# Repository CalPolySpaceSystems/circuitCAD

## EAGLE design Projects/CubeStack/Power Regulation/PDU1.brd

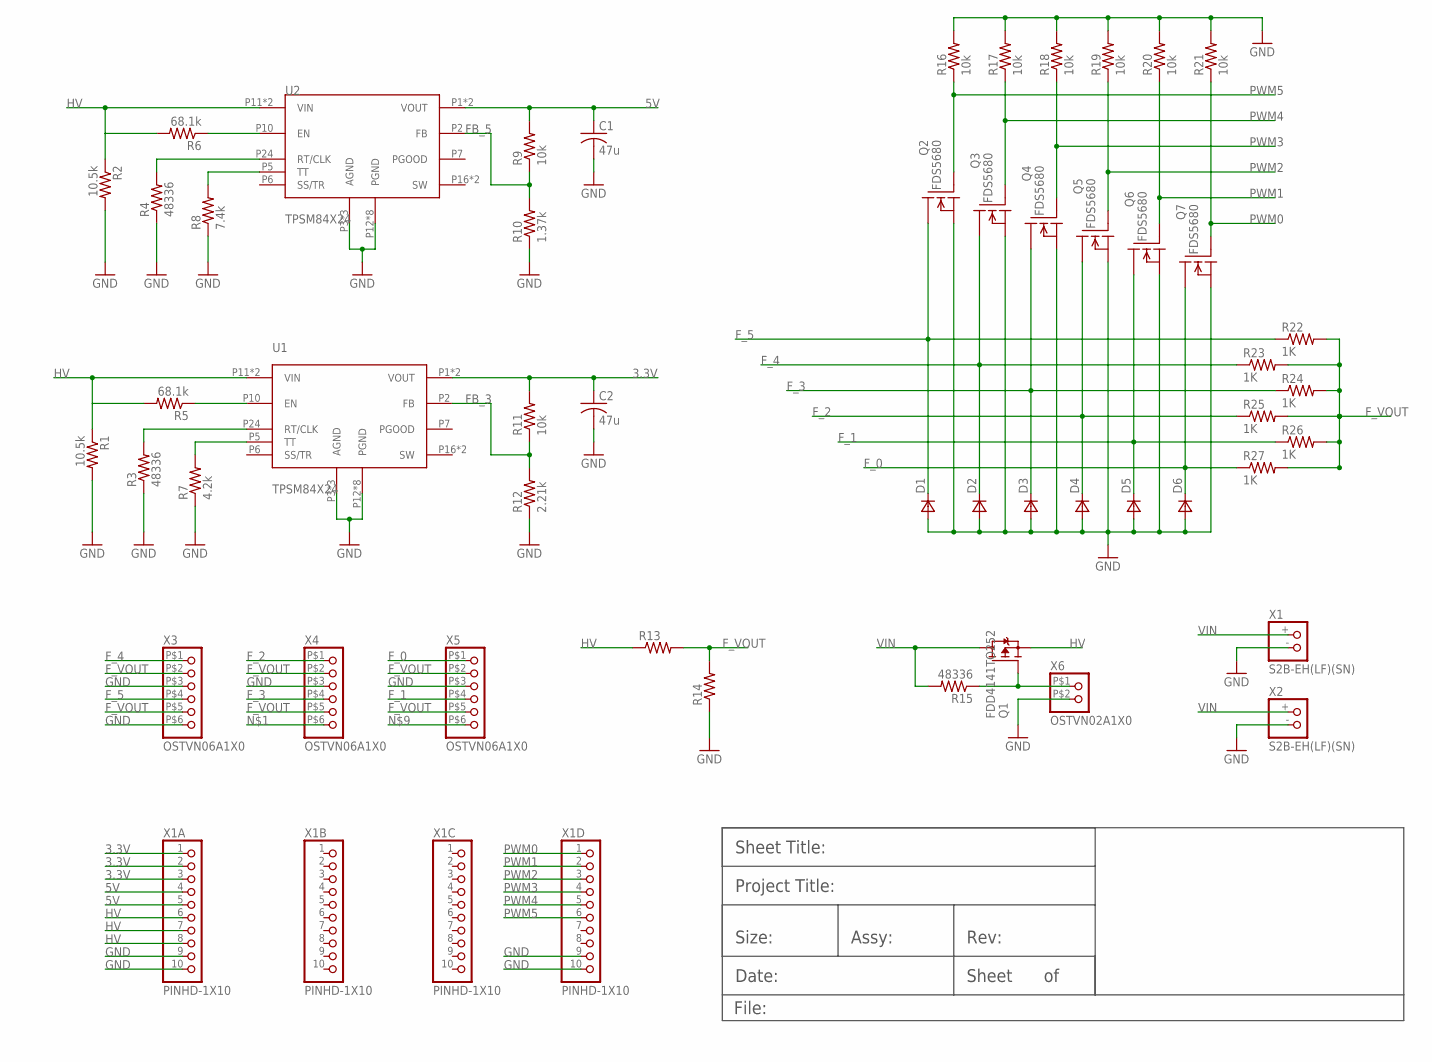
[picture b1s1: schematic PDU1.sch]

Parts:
C1, C2: 47u; C1206
D1, D2, D3, D4, D5, D6: DSOD323; SOD323
Q1: FDD4141TO252; TO252
Q2, Q3, Q4, Q5, Q6, Q7: FDS5680; SO-8
R1, R2: 10.5k; R1206
R3, R4, R15: 48336; R1206
R5, R6: 68.1k; R1206
R7: 4.2k; R1206
R8: 7.4k; R1206
R9, R11: 10k; R1206
R10: 1.37k; R1206
R12: 2.21k; R1206
R13, R14: R-US_R6332; R6332
R16, R17, R18, R19, R20, R21: 10k; R0603
R22, R23, R24, R25, R26, R27: 1K; R0603
U1, U2: TPSM84X24; QFM-5.4
X1, X2: S2B-EH(LF)(SN); S2B-EH
X1A, X1B, X1C, X1D: PINHD-1X10; 1X10-BIG
X3, X4, X5: OSTVN06A1X0
X6: OSTVN02A1X0

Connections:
3.3V: C2.1, R11.2, U1.P1 (VOUT), U1.P8 (VOUT), X1A.1, X1A.2, X1A.3
5V: C1.1, R9.2, U2.P1 (VOUT), U2.P8 (VOUT), X1A.4, X1A.5
EN: Q1.1 (G), R15.1, X6.P$1 (1)
FB_3: R11.1, R12.2, U1.P2 (FB)
FB_5: R9.1, R10.2, U2.P2 (FB)
F_0: D6.1 (C), Q7.5 (D), Q7.6 (D), Q7.7 (D), Q7.8 (D), R27.1, X5.P$1 (1)
F_1: D5.1 (C), Q6.5 (D), Q6.6 (D), Q6.7 (D), Q6.8 (D), R26.1, X5.P$4 (4)
F_2: D4.1 (C), Q5.5 (D), Q5.6 (D), Q5.7 (D), Q5.8 (D), R25.1, X4.P$1 (1)
F_3: D3.1 (C), Q4.5 (D), Q4.6 (D), Q4.7 (D), Q4.8 (D), R24.1, X4.P$4 (4)
F_4: D2.1 (C), Q3.5 (D), Q3.6 (D), Q3.7 (D), Q3.8 (D), R23.1, X3.P$1 (1)
F_5: D1.1 (C), Q2.5 (D), Q2.6 (D), Q2.7 (D), Q2.8 (D), R22.1, X3.P$4 (4)
F_VOUT: R13.2, R14.2, R22.2, R23.2, R24.2, R25.2, R26.2, R27.2, X3.P$2 (2), X3.P$5 (5), X4.P$2 (2), X4.P$5 (5), X5.P$2 (2), X5.P$5 (5)
GND: C1.2, C2.2, D1.2 (A), D2.2 (A), D3.2 (A), D4.2 (A), D5.2 (A), D6.2 (A), Q2.1 (S), Q2.2 (S), Q2.3 (S), Q3.1 (S), Q3.2 (S), Q3.3 (S), Q4.1 (S), Q4.2 (S), Q4.3 (S), Q5.1 (S), Q5.2 (S), Q5.3 (S), Q6.1 (S), Q6.2 (S), Q6.3 (S), Q7.1 (S), Q7.2 (S), Q7.3 (S), R1.2, R2.2, R3.1, R4.1, R7.1, R8.1, R10.1, R12.1, R14.1, R16.2, R17.2, R18.2, R19.2, R20.2, R21.2, U1.P3 (AGND), U1.P9 (AGND), U1.P12 (PGND), U1.P13 (PGND), U1.P14 (PGND), U1.P15 (PGND), U1.P18 (PGND), U1.P19 (PGND), U1.P20 (PGND), U1.P21 (PGND), U1.P23 (AGND), U2.P3 (AGND), U2.P9 (AGND), U2.P12 (PGND), U2.P13 (PGND), U2.P14 (PGND), U2.P15 (PGND), U2.P18 (PGND), U2.P19 (PGND), U2.P20 (PGND), U2.P21 (PGND), U2.P23 (AGND), X1.- (2), X1A.9, X1A.10, X1D.9, X1D.10, X2.- (2), X3.P$3 (3), X3.P$6 (6), X4.P$3 (3), X5.P$3 (3), X6.P$2 (2)
HV: Q1.2 (S), R1.1, R2.1, R5.2, R6.2, R13.1, U1.P11 (VIN), U1.P22 (VIN), U2.P11 (VIN), U2.P22 (VIN), X1A.6, X1A.7, X1A.8
unnamed: R4.2, U2.P24 (RT/CLK)
unnamed: R7.2, U1.P5 (TT)
unnamed: R3.2, U1.P24 (RT/CLK)
unnamed: R8.2, U2.P5 (TT)
unnamed: R6.1, U2.P10 (EN)
unnamed: R5.1, U1.P10 (EN)
PWM0: Q7.4 (G), R21.1, X1D.1
PWM1: Q6.4 (G), R20.1, X1D.2
PWM2: Q5.4 (G), R19.1, X1D.3
PWM3: Q4.4 (G), R18.1, X1D.4
PWM4: Q3.4 (G), R17.1, X1D.5
PWM5: Q2.4 (G), R16.1, X1D.6
VIN: Q1.3 (D), R15.2, X1.+ (1), X2.+ (1)

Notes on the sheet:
C:/Users/patri/Pictures/CPSSLOGO.bmp

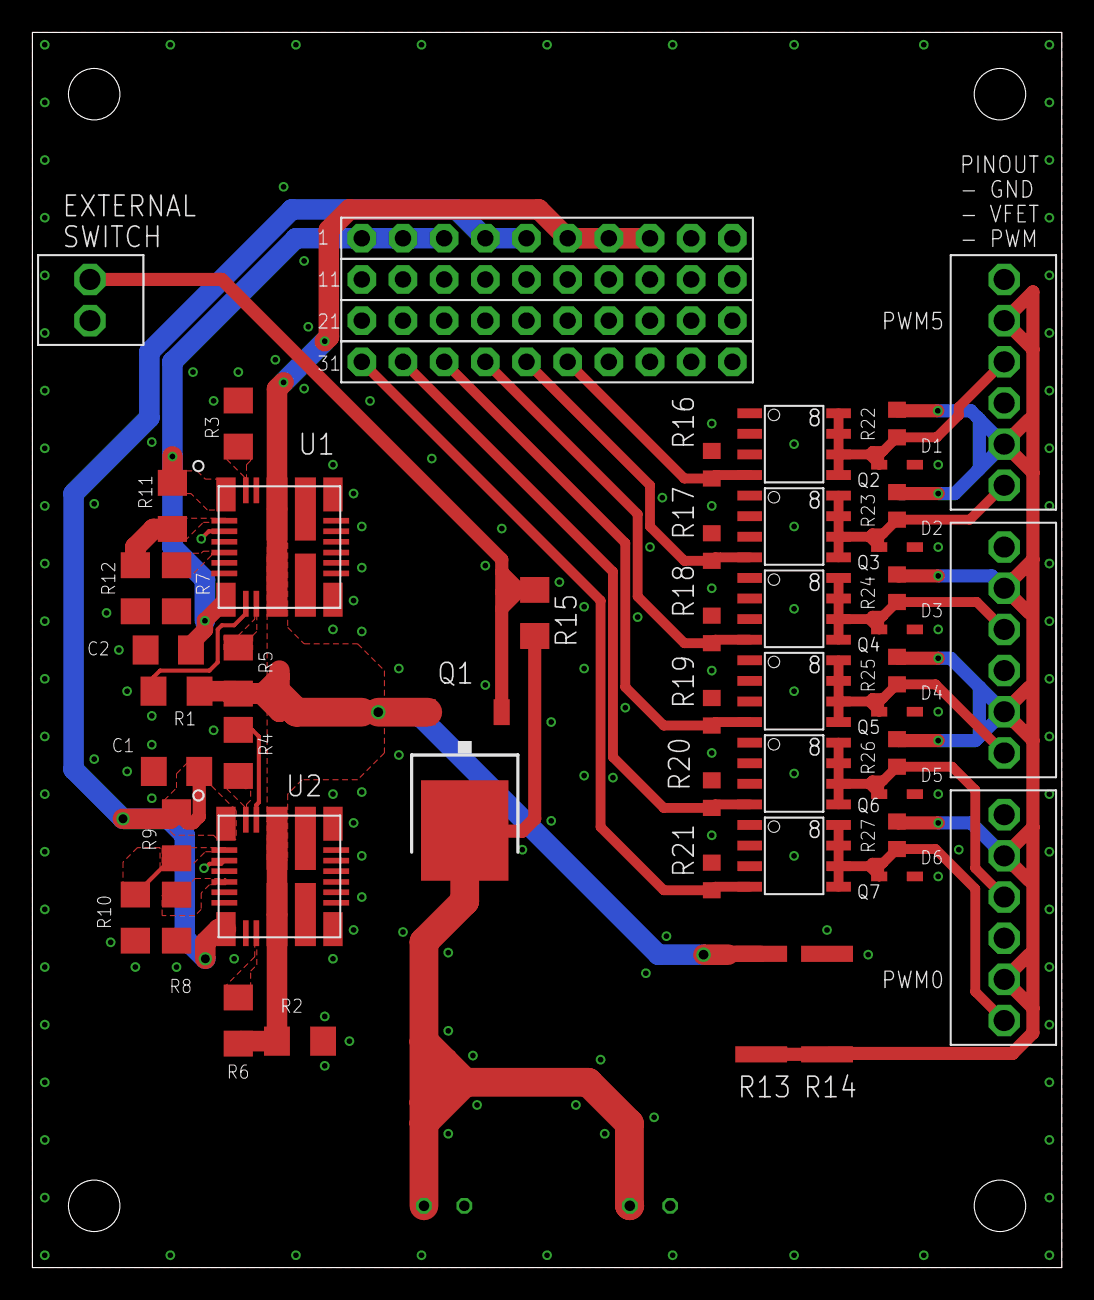
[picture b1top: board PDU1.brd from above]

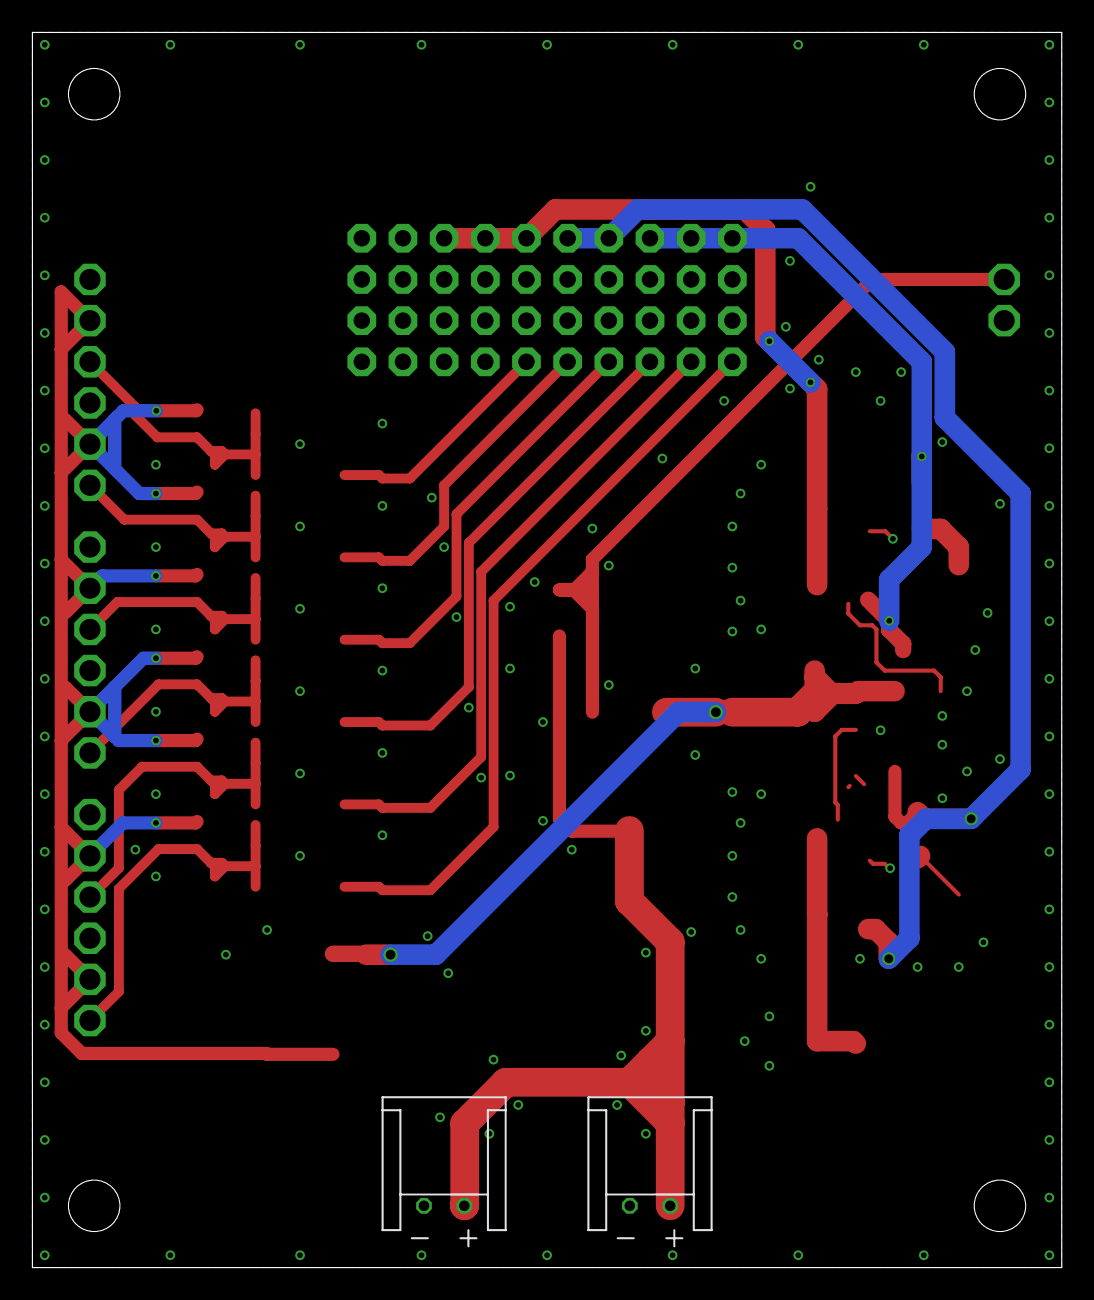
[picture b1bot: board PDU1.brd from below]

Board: 2 copper layers, 63.5 x 76.2 mm, 54 parts (2 on the bottom side), 27 nets.

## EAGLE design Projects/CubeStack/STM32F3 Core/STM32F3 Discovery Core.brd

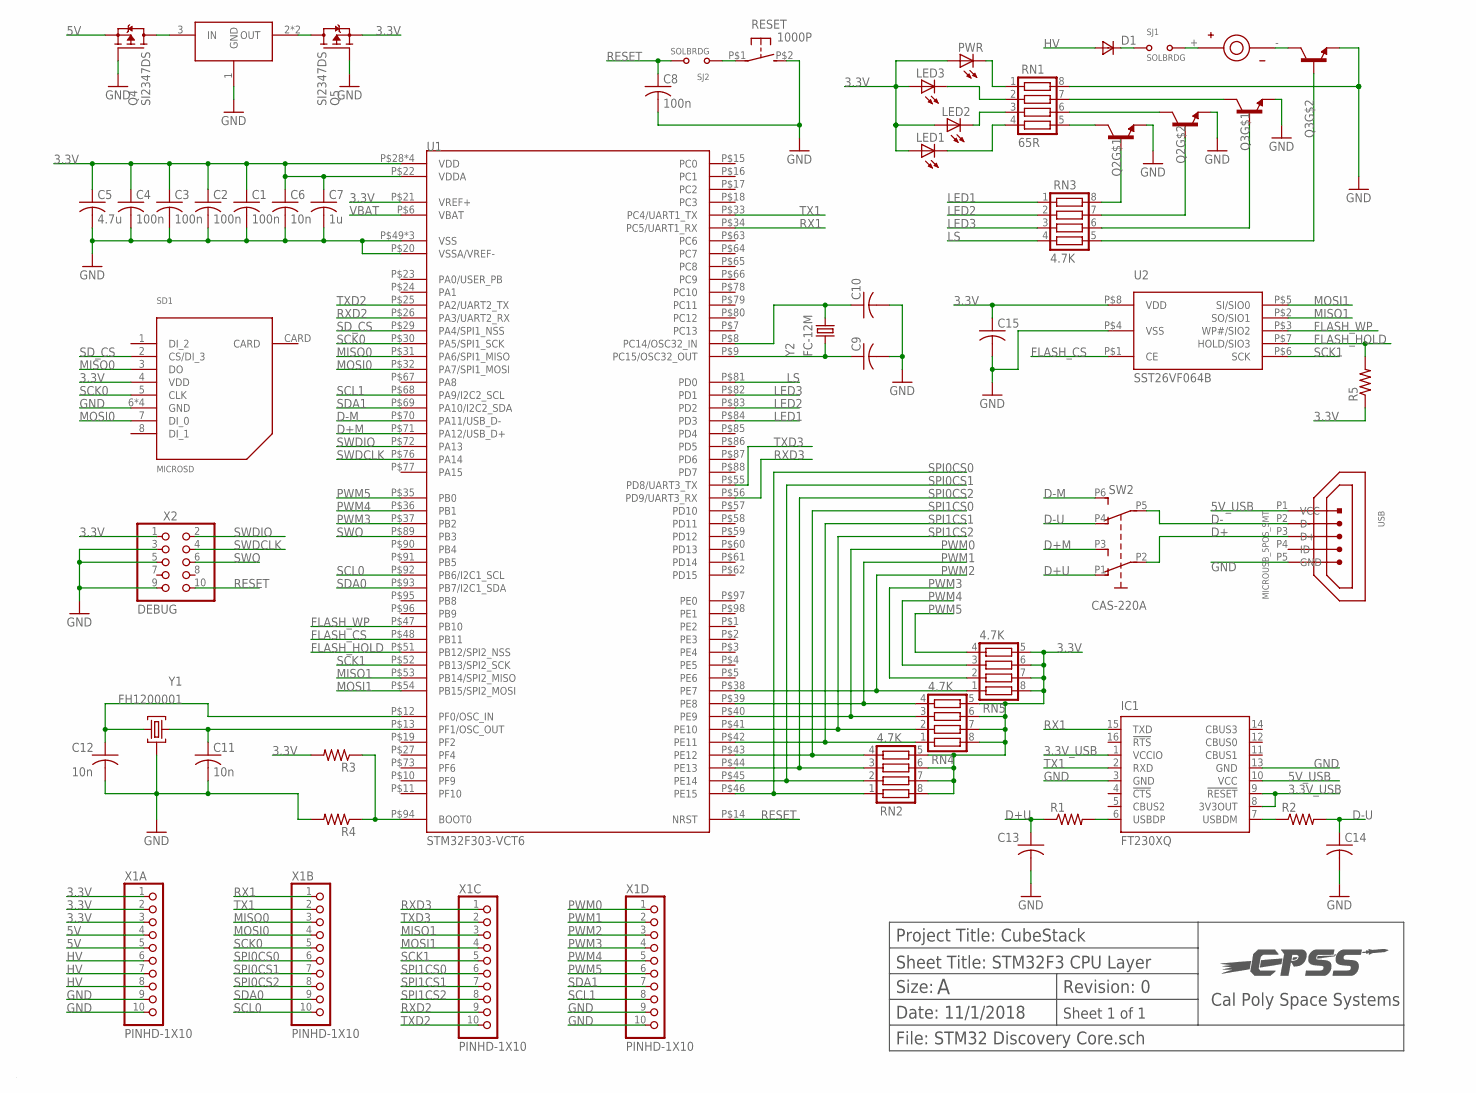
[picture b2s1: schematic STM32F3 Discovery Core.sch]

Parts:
C1, C2, C3, C4: 100n; C0805
C5: 4.7u; C0805
C6: 10n; C0805
C7: 1u; C0805
C8: 100n; C0603
C9, C10, C15: C-USC0402; C0402
C11, C12: 10n; C0402
C13, C14: C-USC0603; C0603
D1: DSOD323; SOD323
IC1: FT230XQ; QFN16
LED1, LED2, LED3: LEDCHIPLED_0805; CHIPLED_0805
LS1: AI-1440-TWT-24V-2-R; AI-1440-TWT-24-2-R
PWR: LEDCHIPLED_0805; CHIPLED_0805
Q2, Q3: MBT3904DW2T1; SOT-363
Q4, Q5: SI2347DS; SOT23
R1, R2, R3, R4, R5: R-US_R0603; R0603
RESET: 1000P; B3U-1000P
RN1: 65R; CTS742C083
RN2, RN3, RN4, RN5: 4.7K; CTS742C083
SD1: MICROSD; CONN_MICROSD
SJ1, SJ2: SOLBRDG
SW2: CAS-220A; CAS220B1
U1: STM32F303-VCT6; LQFP-100
U2: SST26VF064B; SOIJ
U3: AZ1117C; SOT89
USB: MICROUSB_5POS_SMT; RECPT_SMT_R/A
X1A, X1B, X1C, X1D: PINHD-1X10; 1X10-BIG
X2: DEBUG; 2X5-PTH-1.27MM
Y1: FH1200001; MINISMD
Y2: FC-12M

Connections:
3.3V: C1.1, C2.1, C3.1, C4.1, C5.1, C6.1, C7.1, C15.1, LED1.A, LED2.A, LED3.A, PWR.A, Q5.2 (S), R3.2, R5.1, RN2.5, RN2.6, RN2.7, RN2.8, RN4.5, RN4.6, RN4.7, RN4.8, RN5.5, RN5.6, RN5.7, RN5.8, SD1.4 (VDD), U1.P$21 (VREF+), U1.P$22 (VDDA), U1.P$28 (VDD), U1.P$50 (VDD), U1.P$75 (VDD), U1.P$100 (VDD), U2.P$8 (VDD), X1A.1, X1A.2, X1A.3, X2.1
3.3V_USB: IC1.1 (VCCIO), IC1.8 (3V3OUT), IC1.9 (!RESET), Q5.3 (D), U3.2 (OUT), U3.2@1 (OUT)
5V: Q4.2 (S), X1A.4, X1A.5
5V_USB: IC1.10 (VCC), Q4.3 (D), U3.3 (IN), USB.P1 (VCC)
D+: SW2.P2, USB.P3 (D+)
D+M: SW2.P3 (S), U1.P$71 (PA12/USB_D+)
D+U: C13.1, R1.1, SW2.P1 (O)
D-: SW2.P5 (P1), USB.P2 (D-)
D-M: SW2.P6 (S1), U1.P$70 (PA11/USB_D-)
D-U: C14.1, R2.2, SW2.P4 (O1)
FLASH_CS: U1.P$48 (PB11), U2.P$1 (CE)
FLASH_HOLD: R5.2, U1.P$51 (PB12/SPI2_NSS), U2.P$7 (HOLD/SIO3)
FLASH_WP: U1.P$47 (PB10), U2.P$3 (WP#/SIO2)
GND: C1.2, C2.2, C3.2, C4.2, C5.2, C6.2, C7.2, C8.2, C9.2, C10.2, C11.2, C12.2, C13.2, C14.2, C15.2, IC1.3 (GND), IC1.13 (GND), Q2.P$3 (E), Q2.P$6 (E), Q3.P$3 (E), Q3.P$6 (E), Q4.1 (G), Q5.1 (G), R4.2, RESET.P$2 (S), RN1.8, SD1.6 (GND), SD1.GND1 (GND), SD1.GND2 (GND), SD1.GND3 (GND), U1.P$20 (VSSA/VREF-), U1.P$49 (VSS), U1.P$74 (VSS), U1.P$99 (VSS), U2.P$4 (VSS), U3.1 (GND), USB.P5 (GND), X1A.9, X1A.10, X1D.9, X1D.10, X2.3, X2.5, X2.9, Y1.GND2 (2), Y1.GND4 (2)
HV: D1.2 (A), X1A.6, X1A.7, X1A.8
LED1: RN3.1, U1.P$84 (PD3)
LED2: RN3.2, U1.P$83 (PD2)
LED3: RN3.3, U1.P$82 (PD1)
LS: RN3.4, U1.P$81 (PD0)
LS_D: LS1.-, Q3.P$5 (C)
LS_G: Q3.P$1 (B), RN3.5
L_1: LED1.C, RN1.4
L_1_D: Q2.P$4 (C), RN1.5
L_1_G: Q2.P$2 (B), RN3.8
L_2: LED2.C, RN1.3
L_2_D: Q2.P$5 (C), RN1.6
L_2_G: Q2.P$1 (B), RN3.7
L_3: LED3.C, RN1.2
L_3_D: Q3.P$4 (C), RN1.7
L_3_G: Q3.P$2 (B), RN3.6
L_PWR_D: PWR.C, RN1.1
MISO0: SD1.3 (DO), U1.P$31 (PA6/SPI1_MISO), X1B.3
MISO1: U1.P$53 (PB14/SPI2_MISO), U2.P$2 (SO/SIO1), X1C.3
MOSI0: SD1.7 (DI_0), U1.P$32 (PA7/SPI1_MOSI), X1B.4
MOSI1: U1.P$54 (PB15/SPI2_MOSI), U2.P$5 (SI/SIO0), X1C.4
unnamed: LS1.+, SJ1.P$2
unnamed: C10.1, U1.P$8 (PC14/OSC32_IN), Y2.2
unnamed: RESET.P$1, SJ2.P$1
unnamed: C9.1, U1.P$9 (PC15/OSC32_OUT), Y2.1
unnamed: C12.1, U1.P$12 (PF0/OSC_IN), Y1.P3 (3)
unnamed: C11.1, U1.P$13 (PF1/OSC_OUT), Y1.P1 (1)
unnamed: D1.1 (C), SJ1.P$1
unnamed: IC1.6 (USBDP), R1.2
unnamed: IC1.7 (USBDM), R2.1
unnamed: R3.1, R4.1, U1.P$94 (BOOT0)
PWM0: RN4.3, U1.P$40 (PE9), X1D.1
PWM1: RN4.4, U1.P$39 (PE8), X1D.2
PWM2: RN5.1, U1.P$38 (PE7), X1D.3
PWM3: RN5.2, U1.P$37 (PB2), X1D.4
PWM4: RN5.3, U1.P$36 (PB1), X1D.5
PWM5: RN5.4, U1.P$35 (PB0), X1D.6
RESET: C8.1, SJ2.P$2, U1.P$14 (NRST), X2.10
RX1: IC1.15 (TXD), U1.P$34 (PC5/UART1_RX), X1B.1
RXD2: U1.P$26 (PA3/UART2_RX), X1C.9
RXD3: U1.P$56 (PD9/UART3_RX), X1C.1
SCK0: SD1.5 (CLK), U1.P$30 (PA5/SPI1_SCK), X1B.5
SCK1: U1.P$52 (PB13/SPI2_SCK), U2.P$6 (SCK), X1C.5
SCL0: U1.P$92 (PB6/I2C1_SCL), X1B.10
SCL1: U1.P$68 (PA9/I2C2_SCL), X1D.8
SDA0: U1.P$93 (PB7/I2C1_SDA), X1B.9
SDA1: U1.P$69 (PA10/I2C2_SDA), X1D.7
SD_CS: SD1.2 (CS/DI_3), U1.P$29 (PA4/SPI1_NSS)
SPI0CS0: RN2.1, U1.P$46 (PE15), X1B.6
SPI0CS1: RN2.2, U1.P$45 (PE14), X1B.7
SPI0CS2: RN2.3, U1.P$44 (PE13), X1B.8
SPI1CS0: RN2.4, U1.P$43 (PE12), X1C.6
SPI1CS1: RN4.1, U1.P$42 (PE11), X1C.7
SPI1CS2: RN4.2, U1.P$41 (PE10), X1C.8
SWDCLK: U1.P$76 (PA14), X2.4
SWDIO: U1.P$72 (PA13), X2.2
SWO: U1.P$89 (PB3), X2.6
TX1: IC1.2 (RXD), U1.P$33 (PC4/UART1_TX), X1B.2
TXD2: U1.P$25 (PA2/UART2_TX), X1C.10
TXD3: U1.P$55 (PD8/UART3_TX), X1C.2
VBAT: U1.P$6 (VBAT)

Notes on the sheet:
Size:
Revision: 0
Sheet 1 of 1
Date: 11/1/2018
Sheet Title: STM32F3 CPU Layer
Project Title: CubeStack
File: STM32 Discovery Core.sch
Cal Poly Space Systems
C:/Users/patri/Pictures/CPSSLOGO.bmp

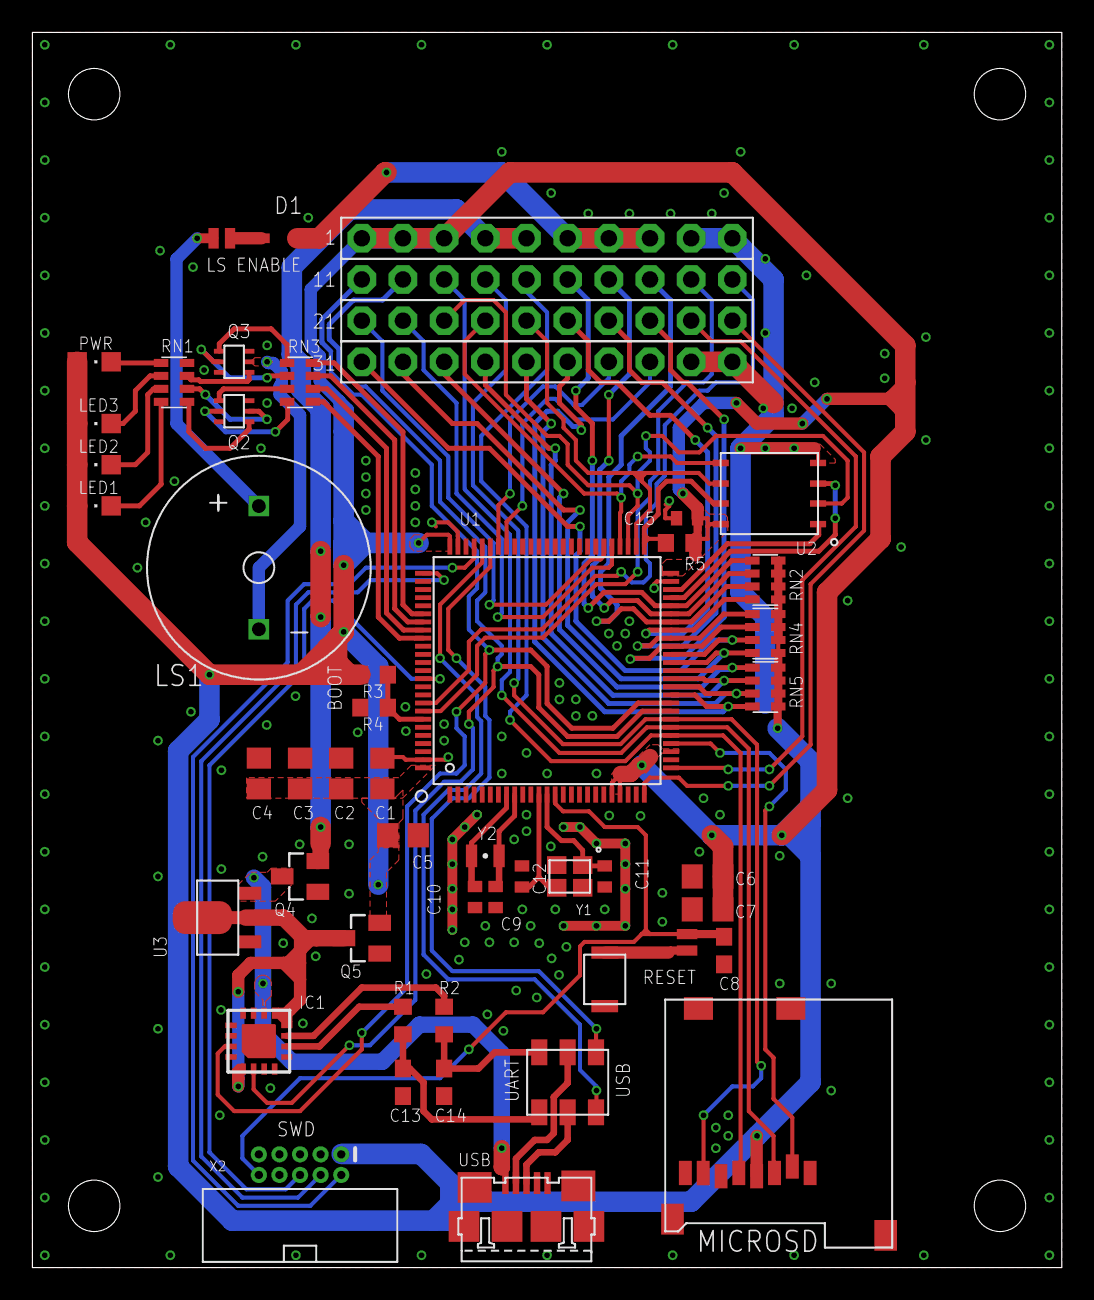
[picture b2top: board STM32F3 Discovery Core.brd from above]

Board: 2 copper layers, 63.5 x 76.2 mm, 52 parts (0 on the bottom side), 74 nets.

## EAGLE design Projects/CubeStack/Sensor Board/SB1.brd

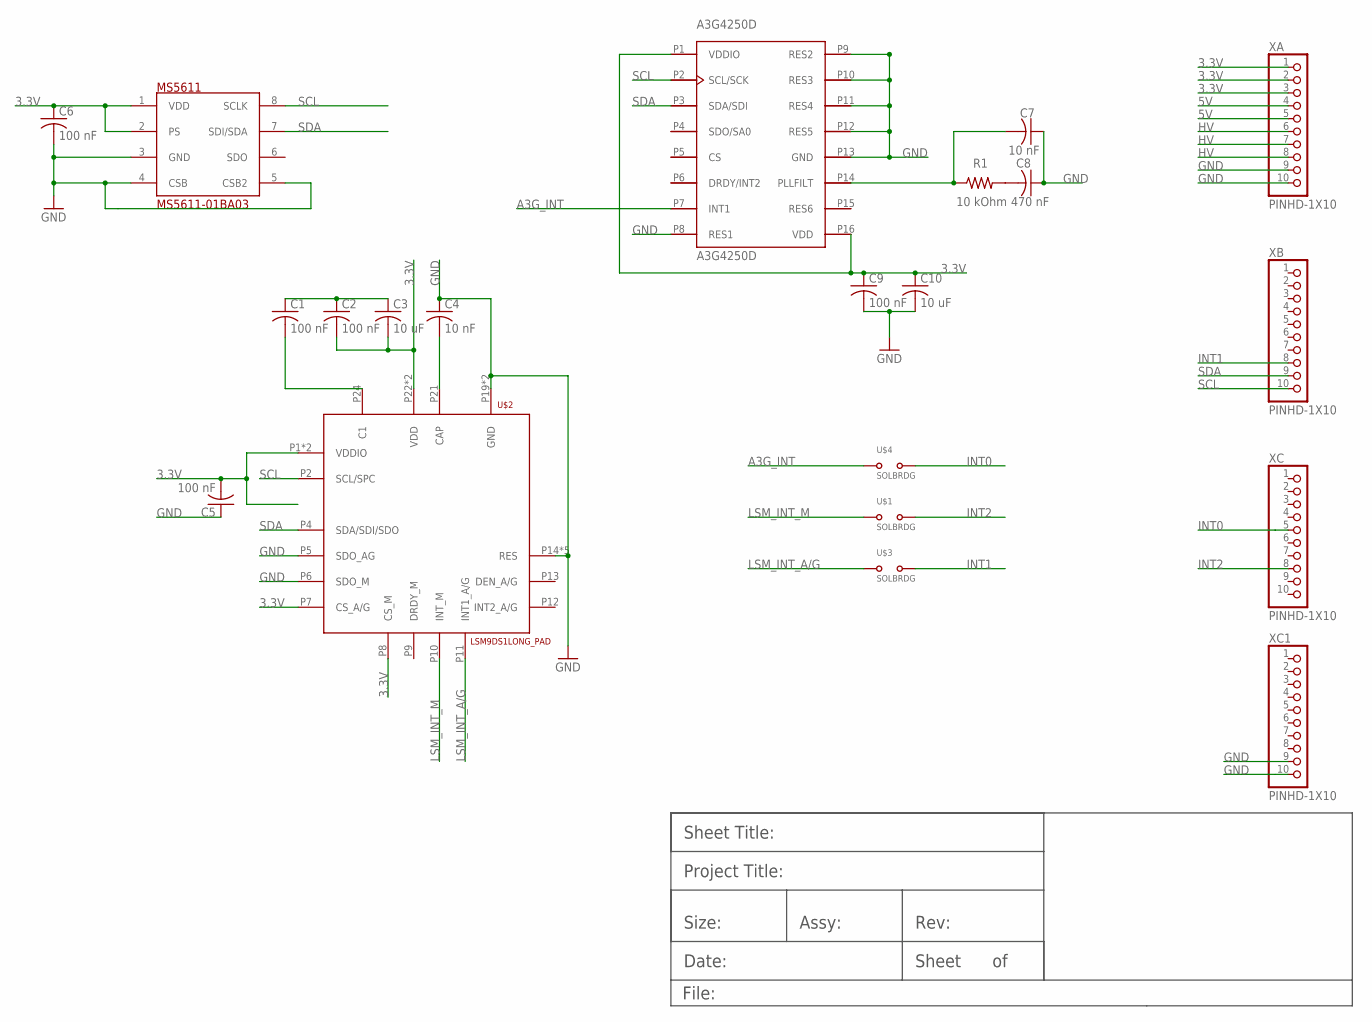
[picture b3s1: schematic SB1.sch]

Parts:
A3G4250D: A3G4250D; LGA-16
C1, C2, C5, C6, C9: 100 nF; C0603
C3, C10: 10 uF; C0603
C4, C7: 10 nF; C0603
C8: 470 nF; C0603
MS5611: MS5611-01BA03
R1: 10 kOhm; R0603
U$1, U$3, U$4: SOLBRDG
U$2: LSM9DS1LONG_PAD; LGA
XA: PINHD-1X10; 1X10-BIG
XB: PINHD-1X10; 1X10-BIG
XC, XC1: PINHD-1X10; 1X10-BIG

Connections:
3.3V: A3G4250D.P1 (VDDIO), A3G4250D.P16 (VDD), C2.2, C3.2, C5.2, C6.1, C9.1, C10.1, MS5611.1 (VDD), MS5611.2 (PS), U$2.P1 (VDDIO), U$2.P3 (VDDIO), U$2.P7 (CS_A/G), U$2.P8 (CS_M), U$2.P22 (VDD), U$2.P23 (VDD), XA.1, XA.2, XA.3
5V: XA.4, XA.5
A3G_INT: A3G4250D.P7 (INT1), U$4.P$1
GND: A3G4250D.P8 (RES1), A3G4250D.P9 (RES2), A3G4250D.P10 (RES3), A3G4250D.P11 (RES4), A3G4250D.P12 (RES5), A3G4250D.P13 (GND), C1.1, C2.1, C3.1, C4.1, C5.1, C6.2, C7.1, C8.1, C9.2, C10.2, MS5611.3 (GND), MS5611.4 (CSB), MS5611.5 (CSB2), U$2.P5 (SDO_AG), U$2.P6 (SDO_M), U$2.P14 (RES), U$2.P15 (RES), U$2.P16 (RES), U$2.P17 (RES), U$2.P18 (RES), U$2.P19 (GND), U$2.P20 (GND), XA.9, XA.10, XC1.9, XC1.10
HV: XA.6, XA.7, XA.8
INT0: U$4.P$2, XC.5
INT1: U$3.P$2, XB.8
INT2: U$1.P$2, XC.8
LSM_INT_A/G: U$2.P11 (INT1_A/G), U$3.P$1
LSM_INT_M: U$1.P$1, U$2.P10 (INT_M)
unnamed: A3G4250D.P14 (PLLFILT), C7.2, R1.1
unnamed: C8.2, R1.2
unnamed: C4.2, U$2.P21 (CAP)
unnamed: C1.2, U$2.P24 (C1)
SCL: A3G4250D.P2 (SCL/SCK), MS5611.8 (SCLK), U$2.P2 (SCL/SPC), XB.10
SDA: A3G4250D.P3 (SDA/SDI), MS5611.7 (SDI/SDA), U$2.P4 (SDA/SDI/SDO), XB.9

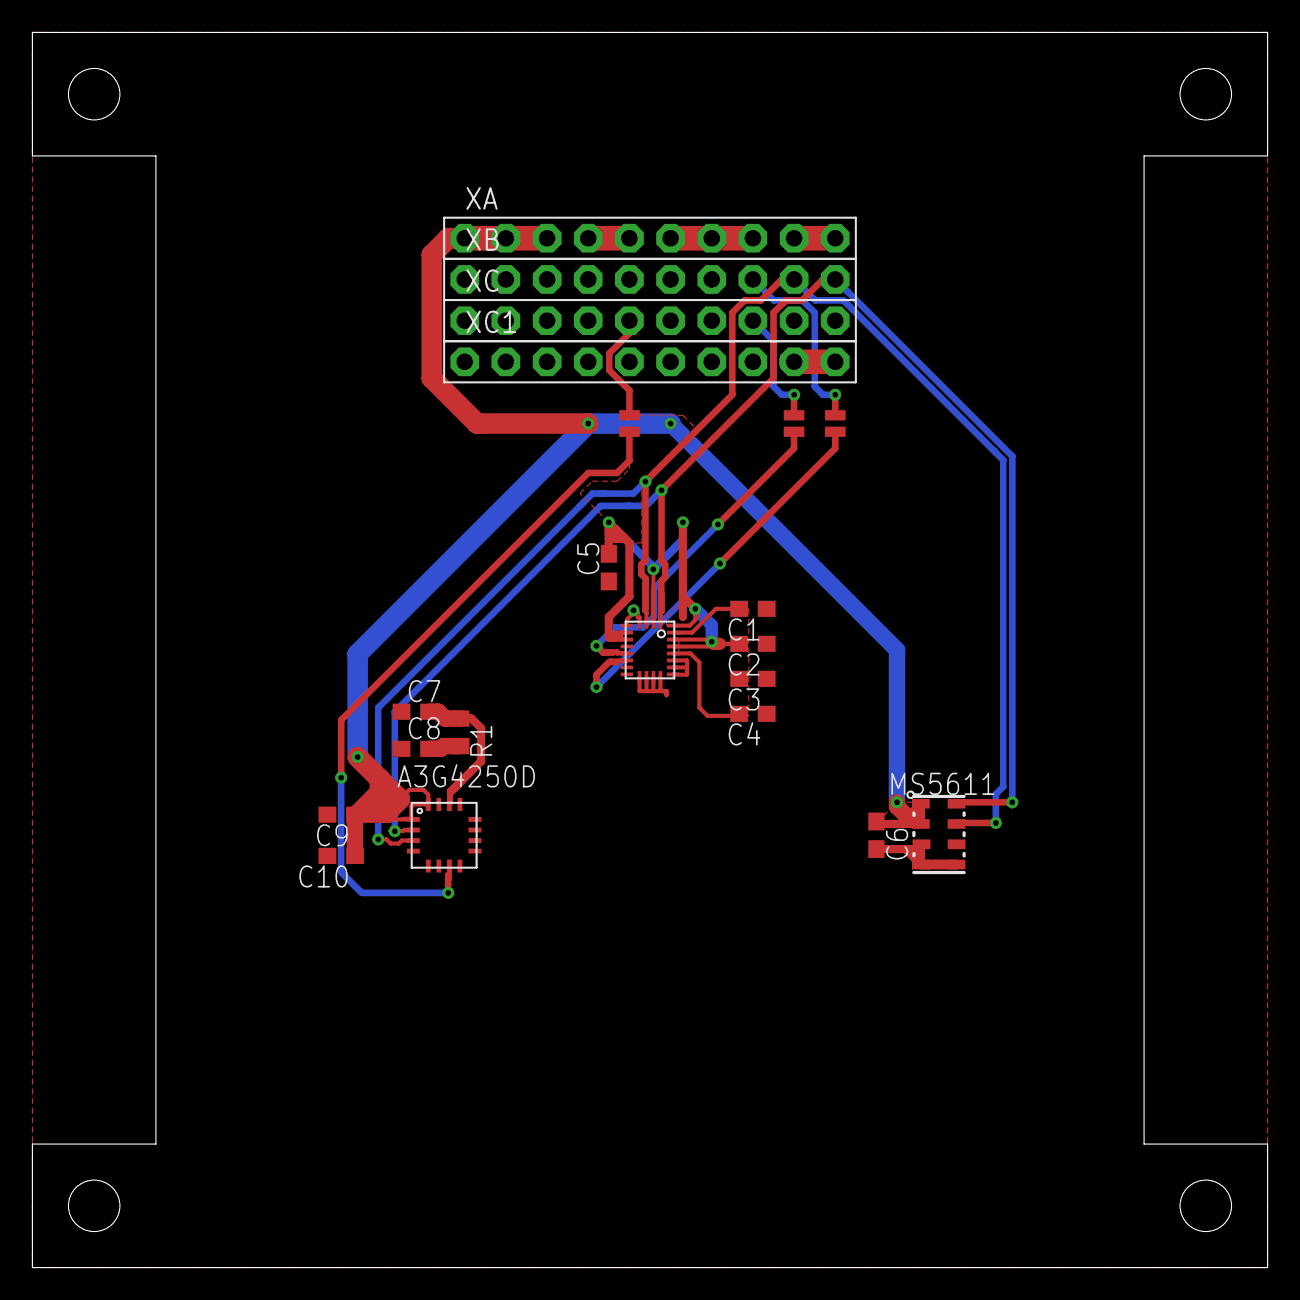
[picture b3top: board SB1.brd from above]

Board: 2 copper layers, 76.2 x 76.2 mm, 21 parts (0 on the bottom side), 16 nets.

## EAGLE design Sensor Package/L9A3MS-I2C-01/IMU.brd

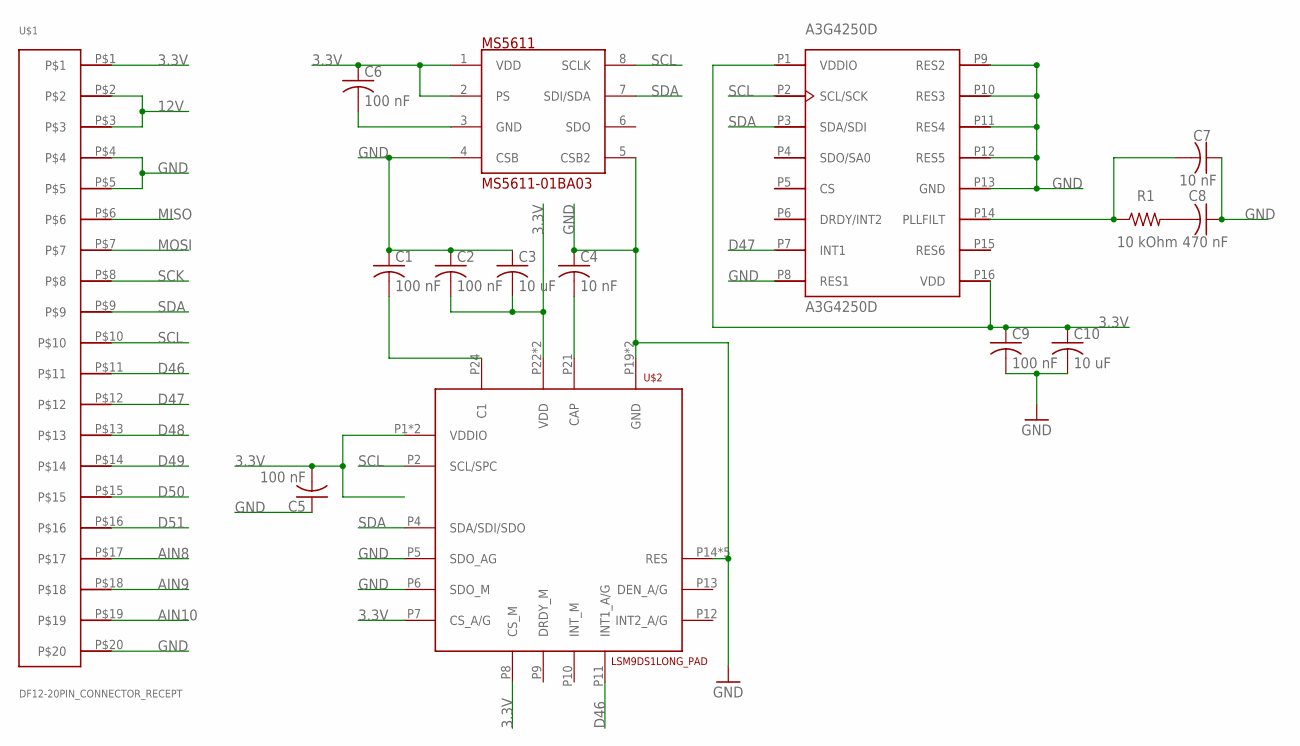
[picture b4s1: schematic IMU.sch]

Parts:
A3G4250D: A3G4250D; LGA-16
C1, C2, C5, C6, C9: 100 nF; C0603
C3, C10: 10 uF; C0603
C4, C7: 10 nF; C0603
C8: 470 nF; C0603
MS5611: MS5611-01BA03
R1: 10 kOhm; R0603
U$1: DF12-20PIN_CONNECTOR_RECEPT; DF12-RECEPT
U$2: LSM9DS1LONG_PAD; LGA

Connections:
3.3V: A3G4250D.P1 (VDDIO), A3G4250D.P16 (VDD), C2.2, C3.2, C5.2, C6.1, C9.1, C10.1, MS5611.1 (VDD), MS5611.2 (PS), U$1.P$1, U$2.P1 (VDDIO), U$2.P3 (VDDIO), U$2.P7 (CS_A/G), U$2.P8 (CS_M), U$2.P22 (VDD), U$2.P23 (VDD)
12V: U$1.P$2, U$1.P$3
AIN8: U$1.P$17
AIN9: U$1.P$18
AIN10: U$1.P$19
D46: U$1.P$11, U$2.P11 (INT1_A/G)
D47: A3G4250D.P7 (INT1), U$1.P$12
D48: U$1.P$13
D49: U$1.P$14
D50: U$1.P$15
D51: U$1.P$16
GND: A3G4250D.P8 (RES1), A3G4250D.P9 (RES2), A3G4250D.P10 (RES3), A3G4250D.P11 (RES4), A3G4250D.P12 (RES5), A3G4250D.P13 (GND), C1.1, C2.1, C3.1, C4.1, C5.1, C7.1, C8.1, C9.2, C10.2, MS5611.4 (CSB), MS5611.5 (CSB2), U$1.P$4, U$1.P$5, U$1.P$20, U$2.P5 (SDO_AG), U$2.P6 (SDO_M), U$2.P14 (RES), U$2.P15 (RES), U$2.P16 (RES), U$2.P17 (RES), U$2.P18 (RES), U$2.P19 (GND), U$2.P20 (GND)
MISO: U$1.P$6
MOSI: U$1.P$7
unnamed: A3G4250D.P14 (PLLFILT), C7.2, R1.1
unnamed: C8.2, R1.2
unnamed: C6.2, MS5611.3 (GND)
unnamed: C4.2, U$2.P21 (CAP)
unnamed: C1.2, U$2.P24 (C1)
SCK: U$1.P$8
SCL: A3G4250D.P2 (SCL/SCK), MS5611.8 (SCLK), U$1.P$10, U$2.P2 (SCL/SPC)
SDA: A3G4250D.P3 (SDA/SDI), MS5611.7 (SDI/SDA), U$1.P$9, U$2.P4 (SDA/SDI/SDO)

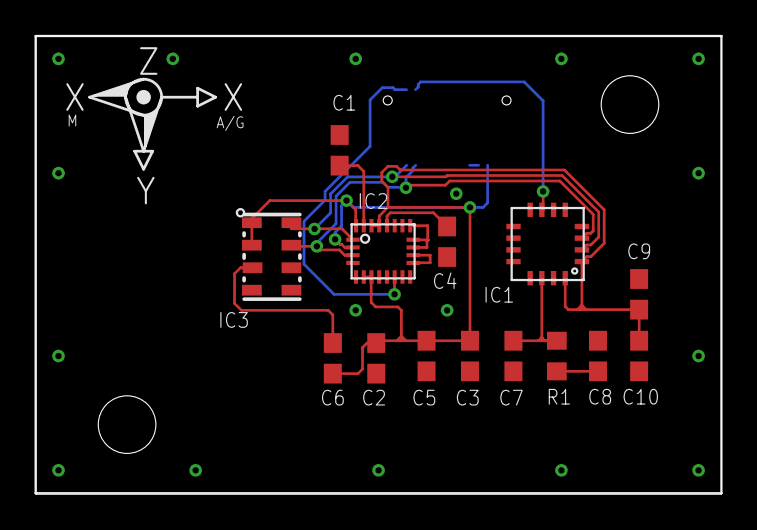
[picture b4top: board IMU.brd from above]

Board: 2 copper layers, 38.1 x 25.5 mm, 15 parts (0 on the bottom side), 12 nets.

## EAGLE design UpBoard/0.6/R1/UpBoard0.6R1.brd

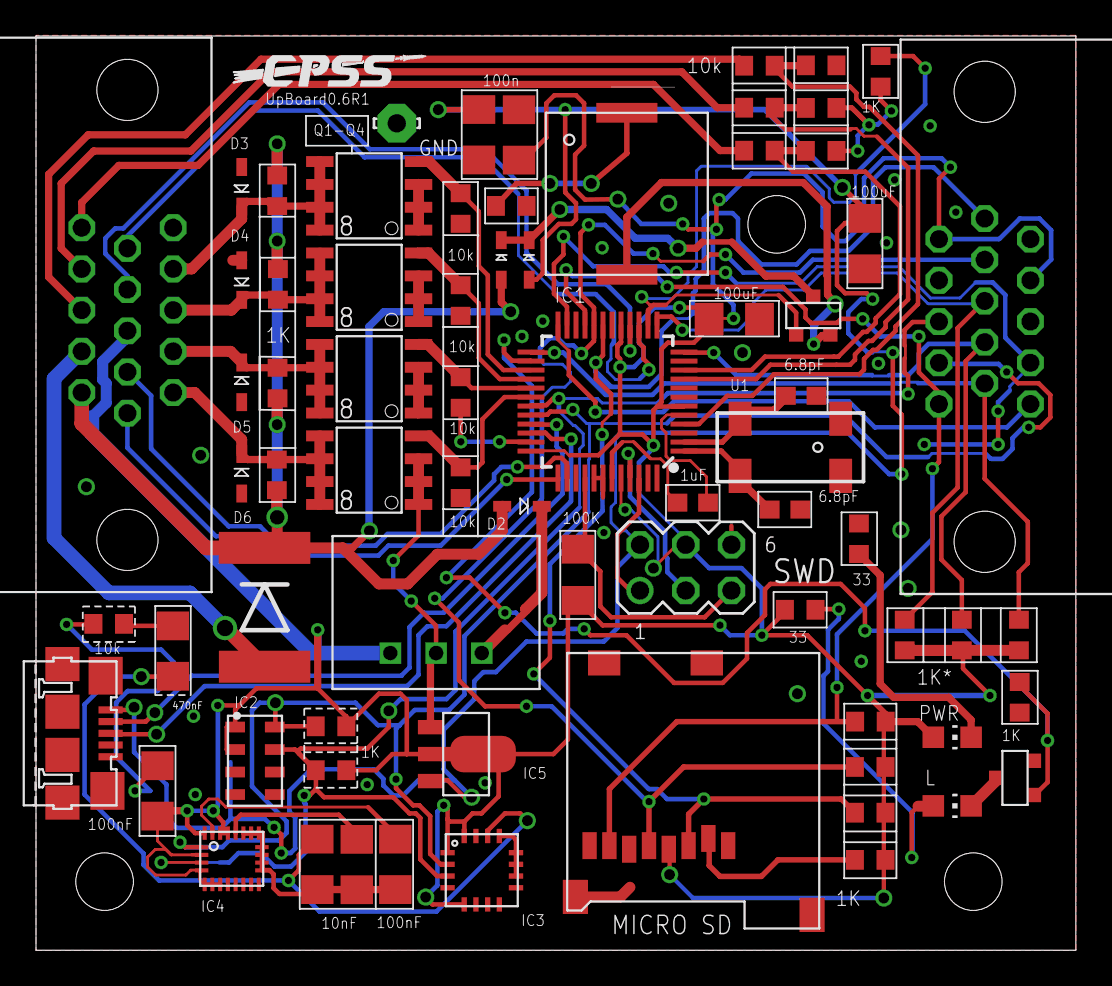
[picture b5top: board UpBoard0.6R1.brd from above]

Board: 2 copper layers, 57.8 x 50.8 mm, 72 parts (0 on the bottom side), 55 nets.

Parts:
C1: 10n; C1206
C2, C5: 100nF; C1206
C3: 10nF; C1206
C4: 470nF; C1206
C6, C7: 6.8pF; C0603
C8: 1uF; C0603
C9, C11: 100n; C1206
C10, C12: 100uF; C1206
D1: S10M-TP; DO-214AB
D2, D3, D4, D5, D6, D7, D8: SOD323
GND: LSP10
IC1: ATSAMD21G-A; TQFP-48
IC2: MS5611-01BA03; 01BA03
IC3: A3G4250D; LGA-16
IC4: LSM9DS1TR; LGA
IC5: AZ1117C; SOT89
L: CHIP-LED0805
MICROUSB: MICROUSB_5POS_SMT; RECPT_SMT_R/A
PWR: CHIP-LED0805
Q1, Q2, Q3, Q4: FDS5680; SO-8
R1: 100K; R1206
R2: 43; R0603
R3, R27: 33; R0603
R4, R5, R6, R7, R8, R9, R20, R21, R22, R23, R24*, R25*, R28, R29: 1K; R0603
R10, R11, R12, R13, R14, R15, R16, R26: 10k; R0603
R17, R18, R19: R0603
R26*: 1K*; R0603
SWD: MA03-2
U1: ABS25
U$4: R-78B3.3-1.5
U$5: PKMCS0909E4000-R1; PKMCS0909E400-R1
U$6, U$13: 15POSD-SUB
U$7, U$12: 2N7002E; NMINI3-R1-B
U$10: CONN_MICROSD

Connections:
3V: C5.1, C11.1, C12.1, IC1.6, IC1.17, IC1.36, IC1.44, IC2.PS, IC2.VDD, IC3.P1, IC3.P5, IC3.P16, IC4.P1, IC4.P3, IC4.P5, IC4.P6, IC4.P7, IC4.P8, IC4.P22, IC4.P23, IC5.2, IC5.2@1, PWR.A, R1.1, R3.2, R4.1, R5.1, R6.1, R7.1, R8.1, R9.1, R24*.1, R25*.1, R26*.1, SWD.4, U$4.3, U$6.1, U$6.12, U$10.4, U$13.8
12V: D1.-, D2.2, D7.2, R20.2, R21.2, R22.2, R23.2, U$13.11
A3: IC1.9, R15.1, R18.1
A4: IC1.10, R16.1, R17.1
AIN0: R15.2, U$13.14
AIN1: R16.2, U$13.15
AREF: IC1.4, R14.1, R19.1
D3: IC1.14, R29.1, U$12.1
D4: IC1.13, R24*.2, U$6.8
D6: IC1.29, Q3.4, R12.1
D7: IC1.30, Q4.4, R13.1
D9: IC1.12, R25*.2, U$6.9
D10: IC1.27, Q1.4, R10.1
D11: IC1.25, R26*.2, U$6.10
D12: IC1.28, Q2.4, R11.1
GND: C1.1, C2.1, C3.2, C5.2, C6.2, C7.2, C8.1, C9.2, C10.2, C11.2, C12.2, D3.2, D4.2, D5.2, D6.2, GND.MP, IC1.5, IC1.18, IC1.35, IC1.41, IC1.42, IC2.CSB1, IC2.CSB2, IC2.GND, IC3.P8, IC3.P9, IC3.P10, IC3.P11, IC3.P12, IC3.P13, IC3.P15, IC4.P14, IC4.P15, IC4.P16, IC4.P17, IC4.P18, IC4.P19, IC4.P20, IC5.1, MICROUSB.P5, Q1.1, Q1.2, Q1.3, Q2.1, Q2.2, Q2.3, Q3.1, Q3.2, Q3.3, Q4.1, Q4.2, Q4.3, R2.1, R10.2, R11.2, R12.2, R13.2, R17.2, R18.2, R19.2, R26.2, R27.2, R28.2, R29.2, SWD.6, U$4.2, U$6.2, U$6.11, U$6.13, U$7.2, U$10.6, U$10.GND1, U$10.GND2, U$10.GND3, U$13.5
LED: IC1.26, R28.1, U$7.1
MISO: IC1.21, R6.2, U$6.5, U$10.7
MOSI: IC1.19, R7.2, U$6.6, U$10.3
unnamed: D2.1, U$4.1
unnamed: R2.2, U$5.P2
unnamed: PWR.C, R27.1
unnamed: U$5.P1, U$12.2
unnamed: D7.1, D8.1, U$12.3
unnamed: C6.1, IC1.2, U1.4
unnamed: C1.2, IC4.P21
unnamed: C2.2, IC4.P24
unnamed: C7.1, IC1.1, U1.1
unnamed: L.A, R3.1
unnamed: C8.2, IC1.43
unnamed: L.C, U$7.3
unnamed: C3.1, C4.1, IC3.P14
unnamed: C4.2, R26.1
RESET: IC1.40, R1.2, SWD.5
RX: IC1.16, U$13.9
RXB: IC1.24, U$6.15
RXD: IC1.38, U$13.7
SCK: IC1.20, R8.2, U$6.7, U$10.5
SCL3: IC1.32, IC2.SCL, IC3.P2, IC4.P2, R5.2, U$6.4
SDA3: IC1.31, IC2.SDI/SDA, IC3.P3, IC4.P4, R4.2, U$6.3
SS3: R9.2, U$10.2
SWDCLK: IC1.45, SWD.3
SWDIO: IC1.46, SWD.1
TX: IC1.15, U$13.10
TXB: IC1.23, U$6.14
TXD: IC1.37, U$13.6
USB_D+: IC1.34, MICROUSB.P3
USB_D-: IC1.33, MICROUSB.P2
VIN: D1.+, U$13.12
VREFIN: R14.2, U$13.13
VUSB: C9.1, C10.1, D8.2, IC5.3, MICROUSB.P1, SWD.2
X_+: D6.1, Q4.5, Q4.6, Q4.7, Q4.8, R20.1, U$13.1
X_-: D4.1, Q2.5, Q2.6, Q2.7, Q2.8, R22.1, U$13.3
Y_+: D5.1, Q3.5, Q3.6, Q3.7, Q3.8, R21.1, U$13.2
Y_-: D3.1, Q1.5, Q1.6, Q1.7, Q1.8, R23.1, U$13.4

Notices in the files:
parts and their libraries:
SparkFun-DigitalIC: Licensing: Creative Commons ShareAlike 4.0 International - https://creativecommons.org/licenses/by-sa/4.0
